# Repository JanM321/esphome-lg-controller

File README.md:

# ESPHome LG AC Wired Controller
Wired controller for LG Air Conditioners using an ESP32 microcontroller and [ESPHome](https://esphome.io/). It can be used to control an indoor unit from [Home Assistant](https://www.home-assistant.io/).

This has some advantages compared to the [LG ThinQ integration](https://github.com/ollo69/ha-smartthinq-sensors):
* Can override the unit's room temperature thermistor with a Home Assistant temperature sensor.
* Does not depend on LG's ThinQ cloud service.
* Supports units without a Wifi module.
* No annoying sounds from the AC unit when changing settings through the controller.
* More settings and information available (although some settings like display light on/off are available in ThinQ but aren't passed to the wired controller).

# Compatibility
### Supported AC units
If your indoor unit supports the LG PREMTB100 and/or LG PREMTA200 controller, it will very likely be compatible.

The [wiki](https://github.com/JanM321/esphome-lg-controller/wiki) has a list of LG AC units that have been tested with this controller.

### Multiple controllers
It's possible to connect multiple controllers to a single indoor unit, but one of them must be set as 'master' and the others as 'slave'. Since February 2024, this ESPHome controller has experimental support for this. I'm not using this myself, so there might be some issues with this (please report them).

The room temperature sensor is ignored for 'slave' controllers, so if you want to use this controller with an LG controller and use a Home Assistant temperature sensor, the LG controller must be set as 'slave'.

### Details
There seem to be two different protocols that LG AC units and wall controllers use to communicate: 
1. **6-byte protocol**: the controller sends a 6-byte message every four seconds or so and the AC unit responds with a 6-byte message. This is the more basic protocol and likely older because it doesn't support advanced features and settings. An ESPHome implementation of this is available here: https://github.com/Flameeyes/esphome-lg-pqrcuds0
2. **13-byte [protocol](protocol.md)**: the controller sends a 13-byte status message every 20 seconds (or when there's a change in settings) and the AC unit sends a very similar status message every 60 seconds. There are also other message types for more advanced settings. **This is the one implemented here.**

The controller hardware is identical because both use a very slow serial connection (104 bps) over a three-wire cable (Red = 12V, Yellow = Signal, Black = GND). In fact, some LG controllers support both protocols: my LG PREMTB001 controller first tries the 13-byte protocol and if it doesn't receive a response it will switch to the 6-byte protocol. My LG PREMTB100 (newer controller) only supports the 13-byte protocol as far as I can tell.

Wired controllers must be connected to the CN-REMO socket on the indoor unit's PCB (green 3 pin JST-XH connector). Fortunately my wall units came with a short extension cable already plugged into that port so I only had to open up the bottom part of the unit to connect my controller.

Wired controllers using the new protocol only send and receive settings and current temperature. The HVAC unit itself decides when to start/stop active cooling/heating etc based on this. It's possible to use a Home Assistant template sensor as temperature sensor to influence this behavior (see below).

See [protocol.md](protocol.md) for information about the protocol based on reverse engineering the PREMTB001 and PREMTB100 controllers.

# Hardware
There are three different PCB designs. The "hardware-tiny" variant is most popular at this point. The "hardware-FeatherS3" PCB is a more recent addition.

## "hardware" (original, June 2023)

You need at least the following parts for each indoor unit:
* PCB. See the original PCB in the [hardware/](hardware/) directory
* ESP32 DevKitC board. I used an Espressif ESP32-DevKitC-32E.
* Cable with JST-XH connector to connect the PCB to the AC. I used an Adafruit 4873 cable.

The `hardware/` PCB I ordered from [PCBWay](https://www.pcbway.com/QuickOrderOnline.aspx).

## "hardware-tiny" (November 2023)

You need at least the following parts for each indoor unit:
* PCB. See the cheaper and smaller PCB in the [hardware-tiny/](hardware-tiny/) directory.
* ESP32 DevKitC board. I used an Espressif ESP32-DevKitC-32E.
* Cable with JST-XH connector to connect the PCB to the AC. I used an Adafruit 4873 cable.

The `hardware-tiny/` PCB can be ordered from [JLCPCB](https://cart.jlcpcb.com/quote/) (see instructions [here](https://github.com/JanM321/esphome-lg-controller/issues/2#issuecomment-1801803656)).

## "hardware-FeatherS3" (May 2025 - updated July 2026)

* rev.20250519 (May 2025)

This revision has a known issue: a 22 uF capacitor is missing at the regulator output (see [this comment](https://github.com/JanM321/esphome-lg-controller/issues/156#issuecomment-4621919638) for details). It is fairly straightforward to rework the PCB to add a capacitor, see [this comment](https://github.com/JanM321/esphome-lg-controller/issues/156#issuecomment-5004138957) for an example.

* rev.20270717 (July 2026)

This is the current revision. Note that the pictures below are for the older revision.

You need at least the following parts for each indoor unit:
* PCB. See the even smaller PCB in the [hardware-FeatherS3/](hardware-FeatherS3/) directory.
* Unexpected Maker's [ESP32 FeatherS3](https://esp32s3.com/feathers3.html)
* Cable with JST-XH connector to connect the PCB to the AC. I used an Adafruit 4873 cable.

This PCB supports the more modern [FeatherS3 by Unexpected Maker](https://esp32s3.com/feathers3.html), which has a USB-C connector. The FeatherS3 [can be powered from the 3.3V pin](https://help.unexpectedmaker.com/index.php/knowledge-base/can-i-power-my-board-from-the-3v3-pin/), which is what is assumed here. The USB-C connector should not be connected at the same time; if you want to power the FeatherS3 via USB, you should not connect the 3.3V pin.

The `hardware-FeatherS3/` PCB can be ordered from [JLCPCB](https://cart.jlcpcb.com/quote/).

JLCPCB ordering instructions:

* Upload [`GERBER-lg_hvac_esp32.zip`](hardware-FeatherS3/jlcpcb/production_files/GERBER-lg_hvac_esp32.zip) as the gerber file, leave all settings default.
* Enable the `Assembly` option at the bottom of the quote page and proceed.
* Upload [`BOM-lg_hvac_esp32.csv`](hardware-FeatherS3/jlcpcb/production_files/BOM-lg_hvac_esp32.csv) for the bom file and [`CPL-lg_hvac_esp32.csv`](hardware-FeatherS3/jlcpcb/production_files/CPL-lg_hvac_esp32.csv) for placement / cpl

I paid about $50 for five boards, fully assembled, before any shipping and import duties.

*Note: if you use the FeatherS3 PCB, you'll also need to make some changes to `esphome/base.yaml` for ESPHome as part of the next step. See the FeatherS3 comments in that file.*

# ESPHome Firmware
I used the following steps to build the ESPHome firmware, flash it on the device, and add the controller in Home Assistant:
1. Clone this repository and navigate to the `esphome` directory.
2. Install ESPHome command line tools on Linux: https://esphome.io/guides/installing_esphome.html
3. Ensure the Python virtual environment is activated (`source venv/bin/activate`).
4. Copy `template.yaml` to (for example) `lg-livingroom.yaml` and edit the lines marked with `XXX`.
5. Connect the ESP32 DevKitC board to your computer with a micro USB cable. This is only needed the first time, after that it can use OTA updates over wifi.
6. Run `esphome run lg-livingroom.yaml` to build the firmware and upload it to the device.
7. The device can now be added in Home Assistant (Settings => Devices & Services). HA will ask you for the encryption key from the YAML file.
8. Disconnect the micro USB cable.
9. Install the ESP32 DevKitC board on the PCB and connect the PCB to the AC.

If you just want to connect to the device to view the debug logs, use `esphome logs lg-livingroom.yaml`.

# Features
Features currently available in Home Assistant:
* Operation mode (off, auto, cool, heat, dry/dehumidify, fan only).
* Target temperature (0.5°C steps).
* Use of a Home Assistant temperature sensor for room temperature (rounded to nearest 0.5°C). 
* Fan speed (slow, low, medium, high, auto).
* Swing mode (off, vertical, horizontal, both).
* Airflow up/down setting from 0-6 for up to 4 vanes (vane angle, with 0 being default for operation mode).
* Switch for external vs internal thermistor.
* Switch for air purifier (plasma) on/off.
* Switch and binary sensor for Auto Dry (also known as Auto Clean) feature. Used to dry indoor unit when it's turned off after cooling/dehumidifying.
* Sensors for reporting outdoor unit on/off, defrost, preheat, error code.
* Sensors for reporting in/mid/out pipe temperatures (if supported by unit).
* Optional passive sensors for total energy and current power, if the unit emits `0xCC`
  or `0xCF` frames on the wired-controller bus.
* Input field for sleep timer from 0 to 420 minutes (0 turns off the sleep timer).
* Input fields for fan speed installer setting (to fine-tune fan speeds, 0-255 with 0 being factory default). This is installer setting 3 (ESP Setting) on LG controllers.
* Select option for over heating installer setting from 0-4 (to change over heating behavior in heating mode). This is installer setting 15 (Over Heating) on LG controllers.
* YAML options for Fahrenheit mode and 'slave' controller mode.
* Detects & exposes only supported operation/fan/swing modes for the connected indoor unit.

The LG ThinQ app and wireless remote can still be used to change these settings and other settings. They'll be synchronized with this controller.

Unfortunately not all settings are exposed to the wired controller, but if you're interested in a feature and it's supported by the PREMTB100 or PREMTA200 controller, please open an issue and we can consider adding it.

The optional energy/power sensors only publish values for units that send the relevant wired-bus
frames. Some LG units expose energy data through ThinQ/WiFi but do not send `0xCC` or `0xCF`
frames to the wired controller; for those units these sensors will not update.

# Tips
* [Issue #43](https://github.com/JanM321/esphome-lg-controller/issues/43) has some information on temperature sensors that work well for this.
* It's possible to use a Home Assistant template sensor as room temperature sensor. I'm [using this](https://gist.github.com/JanM321/b550285713f20231386509b2c227f0b8) to work around some issues with my LG Multi F unit in heating mode.

# PCB (details)
***❗ Update November 2023: This section is for my original PCB in the hardware/ directory. [Florian Brede](https://github.com/florianbrede-ayet) has designed a smaller and cheaper PCB that can be ordered from JLCPCB. It's in the [hardware-tiny/](hardware-tiny/) directory.***

See [hardware/](hardware/) for schematic and list of materials. This part was based on the excellent work and research by [@Flameeyes](https://github.com/Flameeyes):
* https://flameeyes.blog/tag/lg/
* https://github.com/Flameeyes/esphome-lg-pqrcuds0

The hardware needs four main components:
1) **Microcontroller**. Similar to their setup, I used an Espressif ESP32-DevKitC-32E board (it has the ESP32-WROOM-32E module).
A devkit module is nice for this because it doesn't need any external components. My PCB has two female pin headers connecting it to the board. This also makes it easy to replace or upgrade if needed.
2) **Transceiver**. This is needed because the AC has a single (12V) signal wire but the microcontroller has separate (lower-voltage) RX/TX pins. I used a [TI TLIN1027DRQ1](https://www.ti.com/product/TLIN1027-Q1/part-details/TLIN1027DRQ1) LIN transceiver. LIN transceivers are typically used in the automotive industry but work well for this too. As [explained](https://flameeyes.blog/2021/06/29/lg-aircon-reversing-part-2-buses-and-cars/) by Flameeyes, it's important to use a LIN transceiver without the "TXD-Dominant Timeout" feature because LG's very slow ~104 bps serial connection can trigger that timeout and this will corrupt the signal.
3) **Voltage regulator**. This is needed because the AC supplies 12V but the microcontroller requires 3.3V. I replaced the voltage regulator part with a [Traco Power TSRN 1-2433](https://www.tracopower.com/int/model/tsrn-1-2433) step-down switching regulator because it doesn't require any external components such as capacitors or inductors. (In hindsight, the [Traco Power TSR 1-2433](https://www.tracopower.com/int/model/tsr-1-2433) might have been better because it's cheaper and has better availability.)
4) **Connector**. To connect the PCB to the AC. I used a screw terminal for this.

My PCB also has some capacitors, resistors and diodes that are based on the TLIN1027DRQ1 data sheet. I'm not sure if these are really necessary but I included them to be safe and it works well. I used SMT components if available because I had the PCBs assembled by [PCBWay](https://www.pcbway.com/). **Update november 2023: the hardware-tiny/ PCB can be ordered from JLCPCB.**

Note: an alternative for the LIN transceiver is the opto-isolator design used here:
* https://github.com/AussieMakerGeek/LG_Aircon_MQTT_interface
* https://www.instructables.com/Hacking-an-LG-Ducted-Split-for-Home-Automation/

# License
This project is licensed under the 0BSD License. See the LICENSE file for details.
This basically means you can use it however you want. Attribution is not required but would be greatly appreciated.

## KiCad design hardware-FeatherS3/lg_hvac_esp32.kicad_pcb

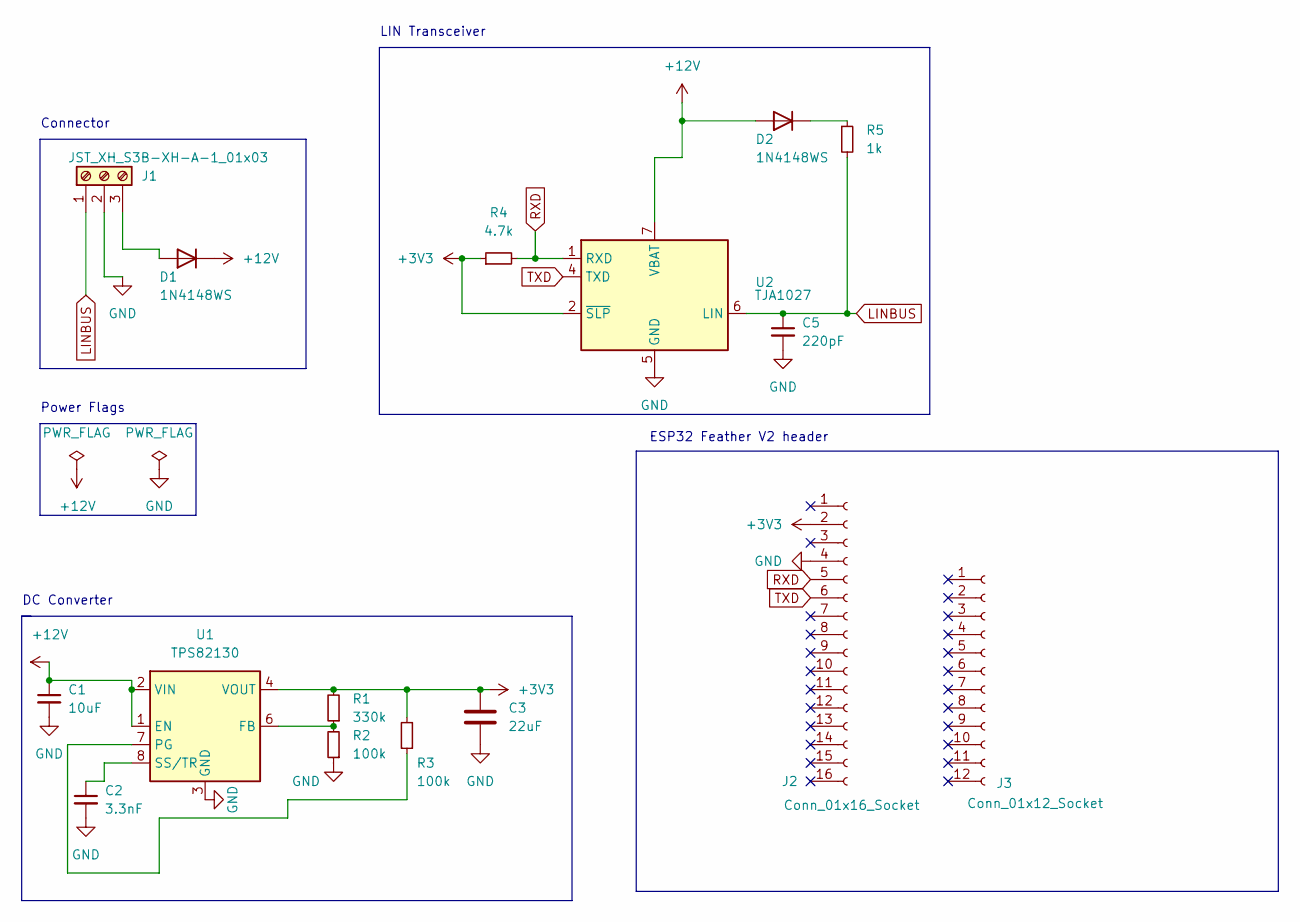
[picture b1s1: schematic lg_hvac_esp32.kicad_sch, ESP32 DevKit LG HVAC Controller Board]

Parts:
C1: 10uF; C_1210_3225Metric; LCSC C92834
C2: 3.3nF; C_0402_1005Metric; LCSC C26404
C3: 22uF; C_0805_2012Metric; LCSC C6119899
C5: 220pF; C_0402_1005Metric; LCSC C343058
D1, D2: 1N4148WS; D_SOD-323; LCSC C727111
J1: JST_XH_S3B-XH-A-1_01x03; JST_XH_S3B-XH-A-1_1x03_P2.50mm_Horizontal; LCSC C157928
J2: Conn_01x16_Socket; PinSocket_1x16_P2.54mm_Vertical
J3: Conn_01x12_Socket; PinSocket_1x12_P2.54mm_Vertical
R1: 330k; R_0805_2012Metric; LCSC C17629
R2, R3: 100k; R_0805_2012Metric; LCSC C149504
R4: 4.7k; R_0805_2012Metric; LCSC C17673
R5: 1k; R_0805_2012Metric; LCSC C17513
U1: TPS82130; Texas_SIL0008D_MicroSiP-8-1EP_2.8x3mm_P0.65mm_EP1.1x1.9mm_T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; LCSC C473914
U2: TJA1027; SOIC-8_3.9x4.9mm_P1.27mm; LCSC C194371

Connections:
+3V3: C3.1, J2.2, R1.2, R3.2, R4.1, U1.4 (VOUT), U1.5 (VOUT), U2.2 (~SLP)
+12V: C1.1, D1.1 (K), D2.2 (A), U1.1 (EN), U1.2 (VIN), U2.7 (VBAT)
GND: C1.2, C2.2, C3.2, C5.2, J1.2, J2.4, R2.1, U1.3 (GND), U1.9 (GND), U2.5 (GND)
LINBUS: C5.1, J1.1, R5.2, U2.6 (LIN)
unnamed: D1.2 (A), J1.3
unnamed: D2.1 (K), R5.1
unnamed: R1.1, R2.2, U1.6 (FB)
unnamed: R3.1, U1.7 (PG)
unnamed: C2.1, U1.8 (SS/TR)
RXD: J2.5, R4.2, U2.1 (RXD)
TXD: J2.6, U2.4 (TXD)

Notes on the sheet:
DC Converter
Connector
LIN Transceiver
Power Flags
ESP32 Feather V2 header

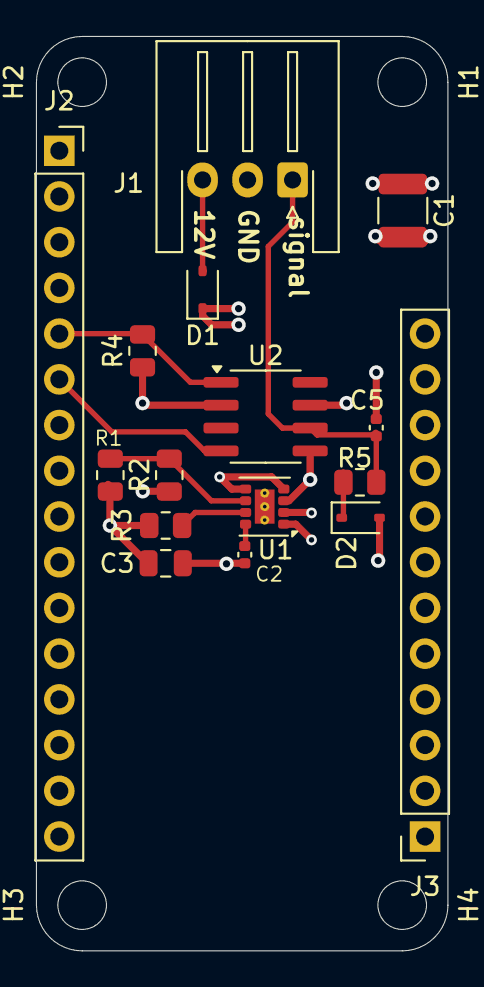
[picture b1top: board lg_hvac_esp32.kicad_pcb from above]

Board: 4 copper layers, 22.9 x 50.8 mm, 20 parts (0 on the bottom side), 11 nets.

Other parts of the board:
H1, H2, H3, H4: MountingHole; MountingHole_2.7mm_M2.5

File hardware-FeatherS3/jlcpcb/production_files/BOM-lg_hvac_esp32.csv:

Comment,Designator,Footprint,LCSC,Quantity
100k,"R2,R3",R_0805_2012Metric,C149504,2
JST_XH_S3B-XH-A-1_01x03,J1,JST_XH_S3B-XH-A-1_1x03_P2.50mm_Horizontal,C157928,1
1k,R5,R_0805_2012Metric,C17513,1
330k,R1,R_0805_2012Metric,C17629,1
4.7k,R4,R_0805_2012Metric,C17673,1
TJA1027,U2,SOIC-8_3.9x4.9mm_P1.27mm,C194371,1
3.3nF,C2,C_0402_1005Metric,C26404,1
Conn_01x12,J3,PinSocket_1x12_P2.54mm_Vertical,C2897375,1
220pF,C5,C_0402_1005Metric,C343058,1
TPS82130,U1,Texas_SIL0008D_MicroSiP-8-1EP_2.8x3mm_P0.65mm_EP1.1x1.9mm_ThermalVias,C473914,1
C_0805_2012Metric,C3,C_0805_2012Metric,C6119899,1
Conn_01x16,J2,PinSocket_1x16_P2.54mm_Vertical,C66987,1
1N4148WS,"D1,D2",D_SOD-323,C727111,2
10uF,C1,C_1210_3225Metric,C92834,1

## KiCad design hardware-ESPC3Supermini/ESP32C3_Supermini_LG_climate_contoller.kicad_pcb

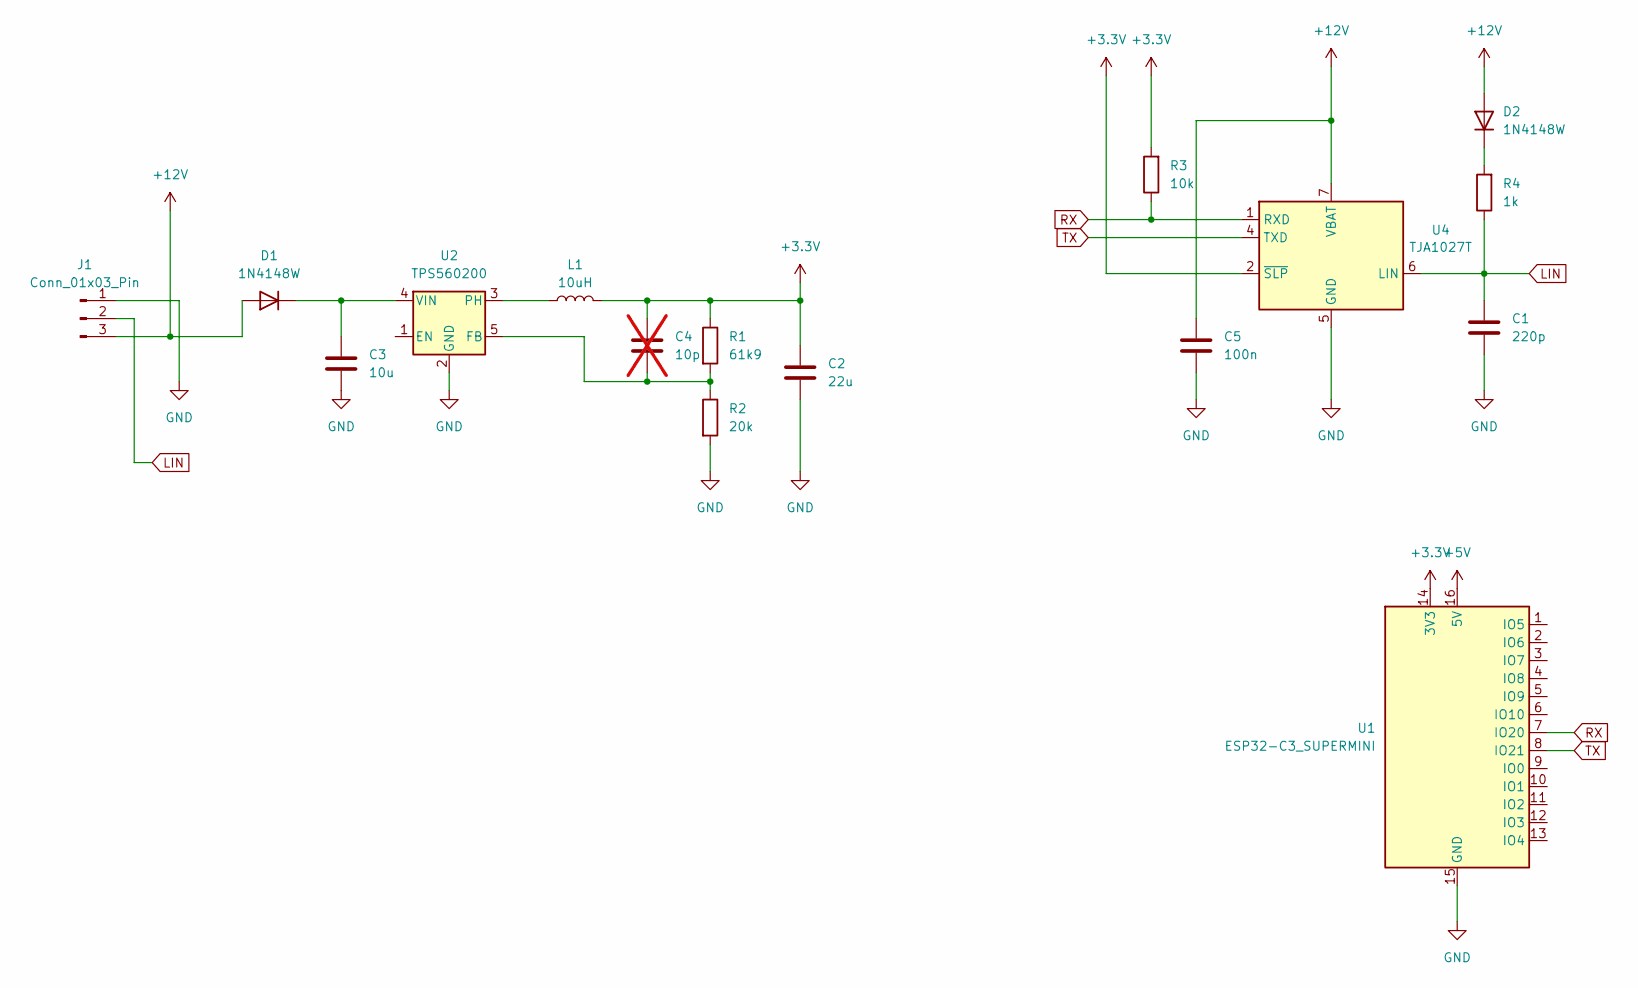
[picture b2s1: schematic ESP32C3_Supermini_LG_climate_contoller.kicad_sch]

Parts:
C1: 220p; C_0402_1005Metric
C2: 22u; C_1206_3216Metric
C3: 10u; C_1206_3216Metric
C4: 10p; C_0402_1005Metric; not fitted
C5: 100n; C_0402_1005Metric
D1, D2: 1N4148W; D_SOD-323; LCSC C2128
J1: Conn_01x03_Pin; CONN_S3B-XH-SM4-TBLFSN_JST
L1: 10uH; L_Wurth_WE-LQSH-3012
R1: 61k9; R_0402_1005Metric
R2: 20k; R_0402_1005Metric
R3: 10k; R_0402_1005Metric
R4: 1k; R_0402_1005Metric
U1: ESP32-C3_SUPERMINI; ESP32-C3 SUPERMINI
U2: TPS560200; SOT-23-5
U4: TJA1027T; SOIC-8_3.9x4.9mm_P1.27mm

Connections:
+3.3V: C2.1, C4.1, L1.2, R1.1, R3.2, U1.14 (3V3), U4.2 (~SLP)
+5V: U1.16 (5V)
+12V: C5.1, D1.2 (A), D2.2 (A), J1.3, U4.7 (VBAT)
GND: C1.2, C2.2, C3.2, C5.2, J1.1, R2.2, U1.15 (GND), U2.2 (GND), U4.5 (GND)
LIN: C1.1, J1.2, R4.1, U4.6 (LIN)
unnamed: C3.1, D1.1 (K), U2.4 (VIN)
unnamed: D2.1 (K), R4.2
unnamed: C4.2, R1.2, R2.1, U2.5 (FB)
unnamed: L1.1, U2.3 (PH)
RX: R3.1, U1.7 (IO20), U4.1 (RXD)
TX: U1.8 (IO21), U4.4 (TXD)

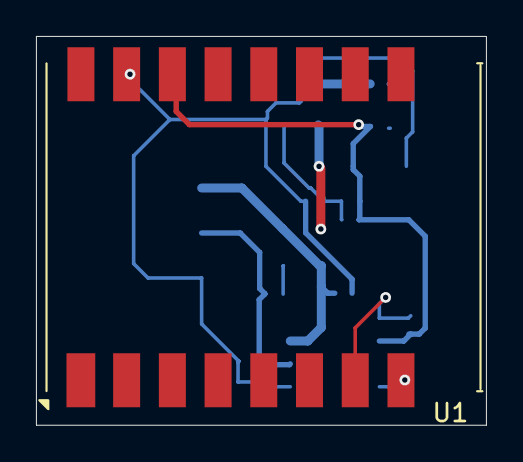
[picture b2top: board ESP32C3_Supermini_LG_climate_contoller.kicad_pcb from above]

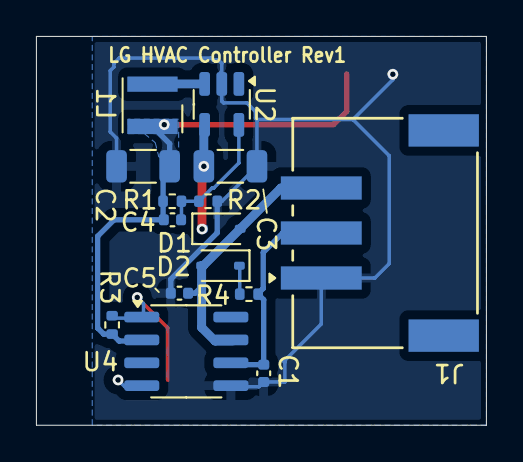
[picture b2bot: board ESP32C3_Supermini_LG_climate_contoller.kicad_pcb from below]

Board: 2 copper layers, 25.0 x 21.6 mm, 16 parts (15 on the bottom side), 10 nets.

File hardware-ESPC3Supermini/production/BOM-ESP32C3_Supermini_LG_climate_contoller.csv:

Comment,Designator,Footprint,LCSC,Quantity
100n,C5,C_0402_1005Metric,C1525,1
10k,R3,R_0402_1005Metric,C25744,1
10u,C3,C_1206_3216Metric,C13585,1
10uH,L1,L_Wurth_WE-LQSH-3012,C5289310,1
1N4148W,"D1,D2",D_SOD-323,C2128,2
1k,R4,R_0402_1005Metric,C11702,1
20k,R2,R_0402_1005Metric,C25765,1
220p,C1,C_0402_1005Metric,C1530,1
22u,C2,C_1206_3216Metric,C12891,1
61k9,R1,R_0402_1005Metric,C25912,1
Conn_01x03_Pin,J1,CONN_S3B-XH-SM4-TBLFSN_JST,C5306495,1
TJA1027T,U4,SOIC-8_3.9x4.9mm_P1.27mm,C194371,1
TPS560200,U2,SOT-23-5,C83671,1
ESP32-C3_SUPERMINI,U1,ESP32-C3 SUPERMINI,,1

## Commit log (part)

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2023-06-16 Fix typo
2023-06-18 Add a very simple AC emulator
2023-06-18 Minor controller improvements (avoid spurious state changes, minor code optimization)
2023-06-22 Minor software improvements
2023-06-30 Add some links to README.md
2023-07-01 Add SVG schematic
2023-07-01 Add higher quality schematic.png
2023-07-01 Add pcb-design.svg
2023-07-01 Add image to README.md
2023-07-01 Rename pcb-design.svg to pcb.svg
2023-07-11 Add BOM and placement CSV files for PCB, fixes #1
2023-07-13 Add list of compatible units to README
2023-07-21 Add ESPHome uptime sensor
2023-07-22 Add higher quality image
2023-07-22 Add higher quality screenshot
2023-07-23 Add better picture
2023-10-30 Improve protocol doc for installer setting 15
2023-11-04 Ignore room temperature from unit if using external sensor. Fixes #10
2023-11-04 Add some more supported models to README
2023-11-04 Make controller initialization match LG controller better
    It now sets the request-settings flag that the LG controller also sets when it's powered on.
    This also handles the settings-batch messages from the AC without (incorrectly) reporting errors.
2023-11-05 Add vertical vane setting and YAML option to set installer setting 15 (for heating mode).
    This required some refactoring to allow sending/processing non-status message types.
2023-11-06 changed minimum temperature setpoint from 18°C to 16°C
2023-11-06 Make initialization code a little more robust
2023-11-07 added hardware-tiny pcb with kicad 6 and production files (setup for jlcpcb assembly)
2023-11-08 Mention new hardware-tiny PCB in the readme
2023-11-10 - added support for parsing & storing capabilities - dynamically show only supported features - support airflow selection of up to 4 vanes - installer settings in UI to fine-tune fan speeds for suppo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
2023-11-10 fixed "slow / quiet" fan speed implementation on restarts, added missing "auto mode" capability, removed unneccessary logs and added comments
2023-11-11 fixed plasma purifier capability detection
2023-11-11 updated readme.md with added features
2023-11-11 Add elevation grill settings to protocol.md
2023-11-11 Only expose fan speed settings if ESP value installer setting is available
2023-11-14 fixed bom and updated kicad project to kicad7 #17
2023-11-18 Add two more supported units to README
2023-12-17 Document pipe temperature values in protocol.md
2023-12-18 Improve AB/CB message documentation
2023-12-18 Add pipe temperature sensors
2023-12-26 Document more bits and messages in protocol.md
2023-12-27 Minor documentation improvements
2024-01-11 Document byte 10 of AA/CA message
2024-01-11 Update protocol.md table format
2024-01-14 Document some bits for zones
2024-01-14 Add information about reservation/timer fields to protocol.md
2024-01-15 Add more information about timers
2024-01-26 Update README, add more supported units
2024-02-01 Add link to template sensor example
2024-02-03 Add sleep timer feature (closes #29)
2024-02-03 Update screenshot and add tiny-pcb picture to README
2024-02-03 Improve README. Link to instructions for ordering the PCB.
2024-02-04 Update protocol.md with more info on reservations
2024-02-05 Add supported ducted unit (closes #30)
2024-02-11 Replace YAML option for over heating (installer setting 15) with a select
2024-02-12 Improve documentation for first message byte (see #33)
2024-02-16 Add initial support for master/slave controllers (closes #34)
2024-02-16 Add Fahrenheit mode based on YAML option (closes #27)
2024-02-16 Add some information about Fahrenheit/Celsius to protocol.md
2024-02-18 Add more supported models to README (closes #36)
2024-02-27 fixes in schematic & bom, removed C3
2024-03-22 Improve protocol documentation
2024-03-22 Add another supported unit
2024-04-08 Update README.md (add supported unit + some minor changes)
2024-04-27 Rewrite as external component (ESPHome custom components are deprecated)
2024-04-27 Fix vane detection issue reported in issue #53 + minor code changes
2024-04-27 Add more supported units
2024-04-28 Move list of supported units to the wiki
2024-05-11 Add switch and binary sensor for Auto Dry (Auto Clean) feature
2024-05-19 Document installer settings a little better in README (issue #56)
2024-06-01 Add explicit uart_id to support configurations with multiple UARTs (fixes #57)
2024-06-13 Queue type a message when a pending status change is sent, so the previous vane setting will be set accordingly
2024-06-19 Make code compatible with ESP-IDF. The main advantage is to be able to use bluetooth proxy to receive BLE temperature sensors
2024-06-22 Use ESPHome interface to check RX pin
2024-06-22 Add ota platform to template.yaml as required by ESPHome 2024.6
2025-01-04 Use 'type: timestamp' for uptime sensor because it's less noisy. Requires a time component to sync time with HA.
2025-05-23 Use climate_schema(..) instead of deprecated CLIMATE_SCHEMA
2025-05-26 Make temp sensor optional
2025-05-28 Add PCB for Unexpected Maker's FeatherS3.
2025-05-29 Add pictures.
2025-06-09 Small changes to README
2025-06-09 Restructure the README a bit
2025-07-10 Update README.md
    Corrected CPL link for featherS3 and type
2025-08-17 Switch from arduino to esp-idf framework (see #119)
2025-09-08 Add buymeacoffee link
2025-11-20 Fix compatibility with ESPHome 2025.11.0
2025-12-24 Support sleep timer for slave controllers (i#136)
2026-01-21 esphome 2026.1.0 callback signature fix
2026-01-21 esphome 2026.1.0 "/" warning fix
2026-02-23 add ESP32C3 Supermini Hardware
2026-02-23 # ESP32C3 HW - move to kicad 9 - add some LCSC part numbers
2026-04-23 Fix climate traits API compatibility
    ESPHome changed the climate traits API from using mask types
    (ClimateModeMask, ClimateFanModeMask, ClimateSwingModeMask) with
    set_supported_modes() to individual add_supported_mode(),
    add_supported_fan_mode(), and add_supported_swing_mode() methods.
    This fix updates configure_capabilities() to use the new API methods.
    The specific ESPHome version where this change occurred is unclear
2026-04-23 Fix climate traits deprecation warnings
    Replace deprecated set_supports_current_temperature(),
    set_supports_two_point_target_temperature(), and set_supports_action()
    with add_feature_flags() to eliminate compilation warnings.
    Note: set_internal() warnings remain as they require dynamic
    runtime decisions based on device capabilities and cannot be
    easily moved to YAML configuration.
2026-05-21 Make compilation possible against esphome 2026.5.0
    Two categories of change
    1. set_internal() deprecation (the only true 2026.5.0 blocker)
    - EntityBase::set_internal() is [[deprecated]] in 2026.3.0, slated for removal in 2027.3.0.
    - The underlying internal_ field was replaced by a 1-bit internal field inside a protected, bit-packed EntityFlags flags_ struct.
    - For LgSwitch/LgSelect/LgNumber (custom subclasses) we add a mark_internal() helper that writes this->flags_.internal directly.
    - For entities the component doesn't subclass (e.g. the plain binary_sensor::BinarySensor* auto_dry_active), we use a small EntityInternalAccess : EntityBase shim that takes a pointer-to-member to the
2026-05-31 Add LG Jet fan mode support
2026-05-31 Add LG power consumption sensors
2026-05-31 Publish climate action status
2026-06-01 Add climate action and status telemetry
2026-06-09 - Change production data. Use JLCPCB Tool Plugin for generation. Add missing LCSC Part number
2026-06-16 Clarify optional LG power sensors
